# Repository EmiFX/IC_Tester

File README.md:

# IC_Tester

[Video Demostración](https://drive.google.com/file/d/17oGDeb1n3LcxcQWol-RU2FpxxYQ4iN93/view?usp=sharing)

## Descripción

**IC_Tester** es un sistema de instrumentación electrónica diseñado para realizar pruebas automatizadas en circuitos integrados de la serie 74xx. Permite verificar el funcionamiento de compuertas lógicas mediante generación de señales digitales y análisis de respuestas.

El sistema está pensado como un prototipo funcional de bajo costo para validación de ICs.

## Características principales

* Prueba automática de compuertas lógicas (PASS / FAIL)
* Generación de señales digitales con microcontrolador
* Comparación contra tablas de verdad
* Monitoreo de corriente en tiempo real (INA219)
* Detección de ICs dañados (pines defectuosos)
* Interfaz en PC para control y visualización

## Arquitectura del sistema

El sistema se compone de:

* **Arduino Nano**: genera señales de prueba y controla el flujo
* **PCB personalizada**: integra todos los componentes
* **Socket ZIF-14**: inserción rápida de ICs
* **INA219**: medición de corriente vía I2C
* **Interfaz en PC**: comunicación serial (VISA)

### Flujo de operación

1. Inserción del IC
2. Aplicación de entradas digitales
3. Lectura de salidas
4. Comparación con valores esperados
5. Resultado final: PASS / FAIL

## Tecnologías utilizadas

* Arduino
* Visual Studio
* LabVIEW (NI-VISA para comunicación serial)
* Diseño de PCB

## Hardware (BOM resumido)

* Arduino Nano
* INA219 Current Sensor
* LM7805 (regulador)
* Socket ZIF-14
* Capacitores y resistencias
* PCB personalizada

## Resultados

* ICs funcionales → `RESULT: PASS`
* ICs dañados → `RESULT: FAIL`
* El sistema identifica correctamente grupos de compuertas defectuosas

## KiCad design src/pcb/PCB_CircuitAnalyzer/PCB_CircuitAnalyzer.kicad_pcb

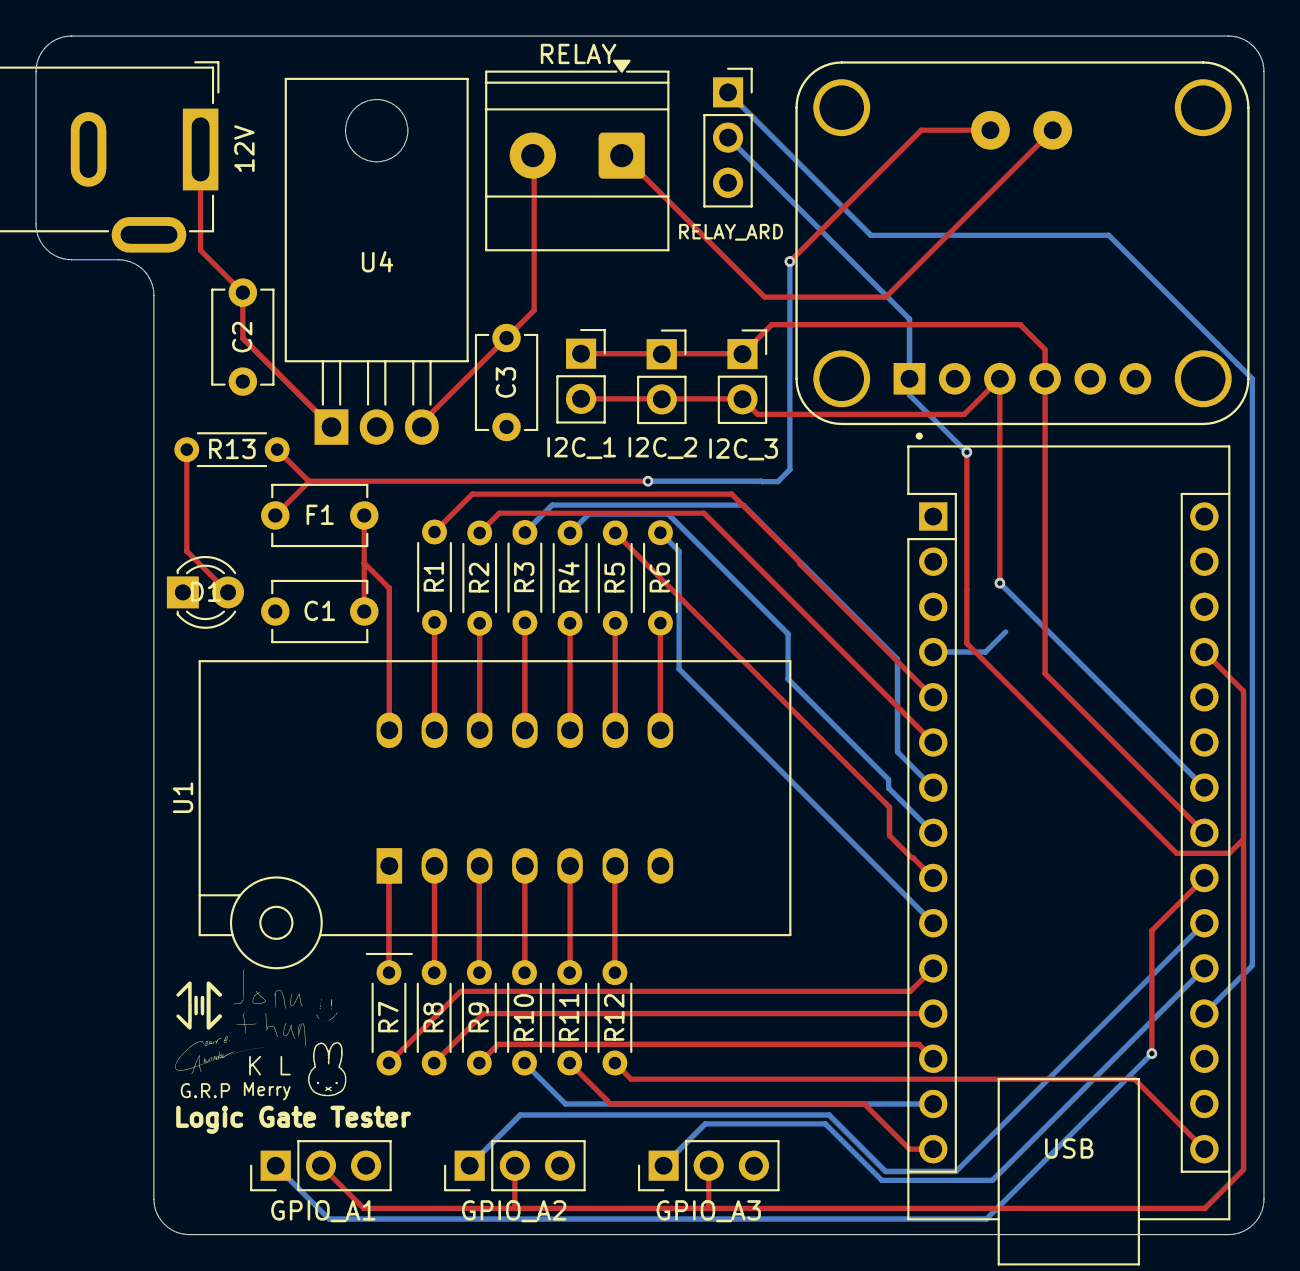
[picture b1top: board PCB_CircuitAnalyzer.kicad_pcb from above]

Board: 2 copper layers, 69.0 x 67.4 mm, 31 parts (0 on the bottom side), 38 nets.

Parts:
12V: Barrel_Jack_MountingPin; BarrelJack_GCT_DCJ200-10-A_Horizontal
A1: Arduino_Nano_v2.x; Arduino_Nano
C1, C3: 0.1uF; C_Disc_D5.1mm_W3.2mm_P5.00mm
C2: 0.33uF; C_Disc_D5.1mm_W3.2mm_P5.00mm
D1: LED; LED_D3.0mm
F1: Polyfuse_Small; C_Disc_D5.1mm_W3.2mm_P5.00mm
GPIO_A1: GPIOA3; PinHeader_1x03_P2.54mm_Vertical
GPIO_A2: GPIOA2; PinHeader_1x03_P2.54mm_Vertical
GPIO_A3: GPIOA1; PinHeader_1x03_P2.54mm_Vertical
I2C_1: I2C_1; PinSocket_1x02_P2.54mm_Vertical
I2C_2: I2C_2; PinSocket_1x02_P2.54mm_Vertical
I2C_3: I2C_3; PinSocket_1x02_P2.54mm_Vertical
R1, R2, R3, R4, R5, R6, R7, R8, R9, R10, R11, R12, R13: 330; R_Axial_DIN0204_L3.6mm_D1.6mm_P5.08mm_Horizontal
RELAY: RELAY; TerminalBlock_Phoenix_MKDS-1,5-2_1x02_P5.00mm_Horizontal
RELAY_ARD: RELAY; PinSocket_1x03_P2.54mm_Vertical
U1: 74LS08; DIP_Socket-14_W4.3_W5.08_W7.62_W10.16_W10.9_3M_214-3339-00-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
U3: 904; MODULE_904
U4: LM7805_TO220; TO-220-3_Horizontal_TabDown

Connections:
+5V: A1.27 (+5V), GPIO_A1.2, GPIO_A2.2, GPIO_A3.2, RELAY_ARD.2, U3.1 (VCC)
+5V_EXT: C3.1, RELAY.2, U4.3 (VO)
+12V: 12V.1, C2.1, U4.1 (VI)
GND: 12V.2, A1.4 (GND), A1.29 (GND), C1.2, C2.2, C3.2, D1.1 (K), GPIO_A1.3, GPIO_A2.3, GPIO_A3.3, RELAY_ARD.3, U1.7 (GND), U3.2 (GND), U4.2 (GND)
GPIOA1: A1.20 (A1), GPIO_A3.1
GPIOA2: A1.21 (A2), GPIO_A2.1
GPIOA3: A1.22 (A3), GPIO_A1.1
IN1: R1.1, U1.13
IN5: R5.1, U1.9
IN7: R7.1, U1.1
IN11: R11.1, U1.5
INOUT2: R2.1, U1.12
INOUT3: R3.1, U1.11
INOUT4: R4.1, U1.10
INOUT8: R8.1, U1.2
INOUT9: R9.1, U1.3
INOUT10: R10.1, U1.4
NO_RELAY: RELAY.1, U3.6 (VIN+), U3.VIN+
unnamed: A1.5 (D2), R1.2
unnamed: A1.6 (D3), R2.2
unnamed: A1.7 (D4), R3.2
unnamed: A1.8 (D5), R4.2
unnamed: A1.9 (D6), R5.2
unnamed: A1.10 (D7), R6.2
unnamed: A1.11 (D8), R7.2
unnamed: A1.12 (D9), R8.2
unnamed: A1.13 (D10), R9.2
unnamed: A1.14 (D11), R10.2
unnamed: A1.15 (D12), R11.2
unnamed: A1.16 (D13), R12.2
unnamed: D1.2 (A), R13.2
unnamed: C1.1, F1.2, U1.14 (VCC)
OUT: F1.1, R13.1, U3.5 (VIN-), U3.VIN-
OUT6: R6.1, U1.8
OUT12: R12.1, U1.6
RELAY: A1.19 (A0), RELAY_ARD.1
SCL: A1.24 (A5), I2C_1.2, I2C_2.2, I2C_3.2, U3.3 (SCL)
SDA: A1.23 (A4), I2C_1.1, I2C_2.1, I2C_3.1, U3.4 (SDA)

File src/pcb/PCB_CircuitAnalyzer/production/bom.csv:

Designator,Footprint,Quantity,Value,LCSC Part #
12V,BarrelJack_GCT_DCJ200-10-A_Horizontal,1,Barrel_Jack_MountingPin,
A1,Arduino_Nano,1,Arduino_Nano_v2.x,
"C1, C3",C_Disc_D5.1mm_W3.2mm_P5.00mm,2,0.1uF,
C2,C_Disc_D5.1mm_W3.2mm_P5.00mm,1,0.33uF,
D1,LED_D3.0mm,1,LED,
F1,C_Disc_D5.1mm_W3.2mm_P5.00mm,1,Polyfuse_Small,
GPIO_A1,PinHeader_1x03_P2.54mm_Vertical,1,GPIOA3,
GPIO_A2,PinHeader_1x03_P2.54mm_Vertical,1,GPIOA2,
GPIO_A3,PinHeader_1x03_P2.54mm_Vertical,1,GPIOA1,
I2C_1,PinSocket_1x02_P2.54mm_Vertical,1,I2C_1,
I2C_2,PinSocket_1x02_P2.54mm_Vertical,1,I2C_2,
I2C_3,PinSocket_1x02_P2.54mm_Vertical,1,I2C_3,
"R1, R10, R11, R12, R13, R2, R3, R4, R5, R6, R7, R8, R9",R_Axial_DIN0204_L3.6mm_D1.6mm_P5.08mm_Horizontal,13,330,
RELAY,"TerminalBlock_Phoenix_MKDS-1,5-2_1x02_P5.00mm_Horizontal",1,RELAY,
RELAY_ARD,PinSocket_1x03_P2.54mm_Vertical,1,RELAY,
U1,DIP_Socket-14_W4.3_W5.08_W7.62_W10.16_W10.9_3M_214-3339-00-0602J,1,74LS08,
U3,MODULE_904,1,904,
U4,TO-220-3_Horizontal_TabDown,1,LM7805_TO220,

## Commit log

2026-05-11 finished schematic
2026-05-12 pcb done
2026-06-04 readme revised
2026-06-04 Added stable files regarding microcontroller firmware and labview panel
2026-06-04 Matched README with main
2026-06-04 Added experimental ml and ocr service files
2026-06-04 added experimental labview panels to interact with ml and ocr services
2026-06-04 Add video demo link to README.md
